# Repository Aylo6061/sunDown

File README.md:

# sunDown
Color temperature tunable lamp.

# Programming over USB
This program pulls the wifi credentials from a file stored in SPIFFS.  This file should be called "creds.txt" and needs to be added to /data.  The contents should be something like:

	{"ssid":"my_network_name", "pwd":"my_secret_password"}

This file is not included, for obvious reasons.  Once this file is in place, proceed to the next step.

Open sunDown.ino in the arduino IDE, and build/upload the code with ctrl+u or the upload button. Once this is done, use the [ESP32 sketch data upload](https://github.com/esp8266/arduino-esp8266fs-plugin) to upload the data folder.

This firmware uses [elegant ota](https://github.com/ayushsharma82/ElegantOTA). Refer to documentation there on running an OTA update.

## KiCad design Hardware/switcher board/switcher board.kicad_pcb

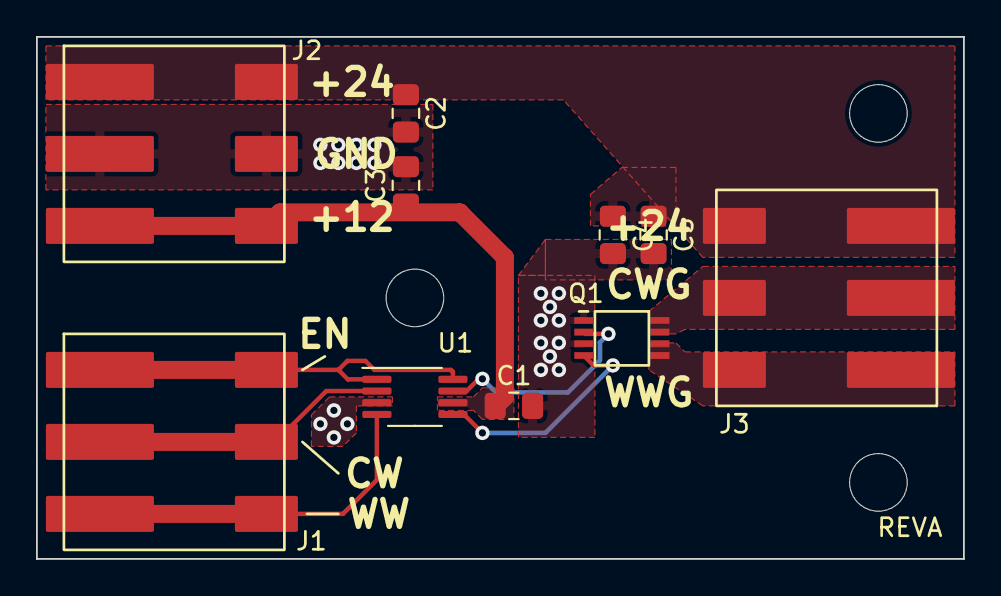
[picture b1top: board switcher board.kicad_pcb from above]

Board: 2 copper layers, 51.5 x 29.0 mm, 13 parts (0 on the bottom side), 10 nets.

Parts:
C1, C2, C3, C4, C5: C; C_0805_2012Metric_Pad1.18x1.45mm_HandSolder
H1, H2, H3: MountingHole; MountingHole_3.2mm_M3
J1, J2, J3: Screw_Terminal_01x03; 2060-453
Q1: IRF7503TRPBF; IR Micro8
U1: MCP14A0154-E/MS; MSOP-8_3x3mm_P0.65mm

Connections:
+12V: C1.1, C3.1, J1.3, U1.6 (Vdd)
+24V: C2.1, C4.1, C5.1, J1.1, J3.3
/CW: J2.2, U1.2 (IN_A)
/CW_Gnd: J3.2, Q1.7 (D2), Q1.8 (D2)
/EN: J2.1, U1.1 (EN_A), U1.8 (EN_B)
/WW: J2.3, U1.4 (IN_B)
/WW_Gnd: J3.1, Q1.5 (D2), Q1.6 (D2)
GND: C1.2, C2.2, C3.2, C4.2, C5.2, J1.2, Q1.1 (S2), Q1.3 (S2), U1.3 (GND)
unnamed: Q1.2 (G2), U1.7 (OUT_A)
unnamed: Q1.4 (G2), U1.5 (OUT_B)

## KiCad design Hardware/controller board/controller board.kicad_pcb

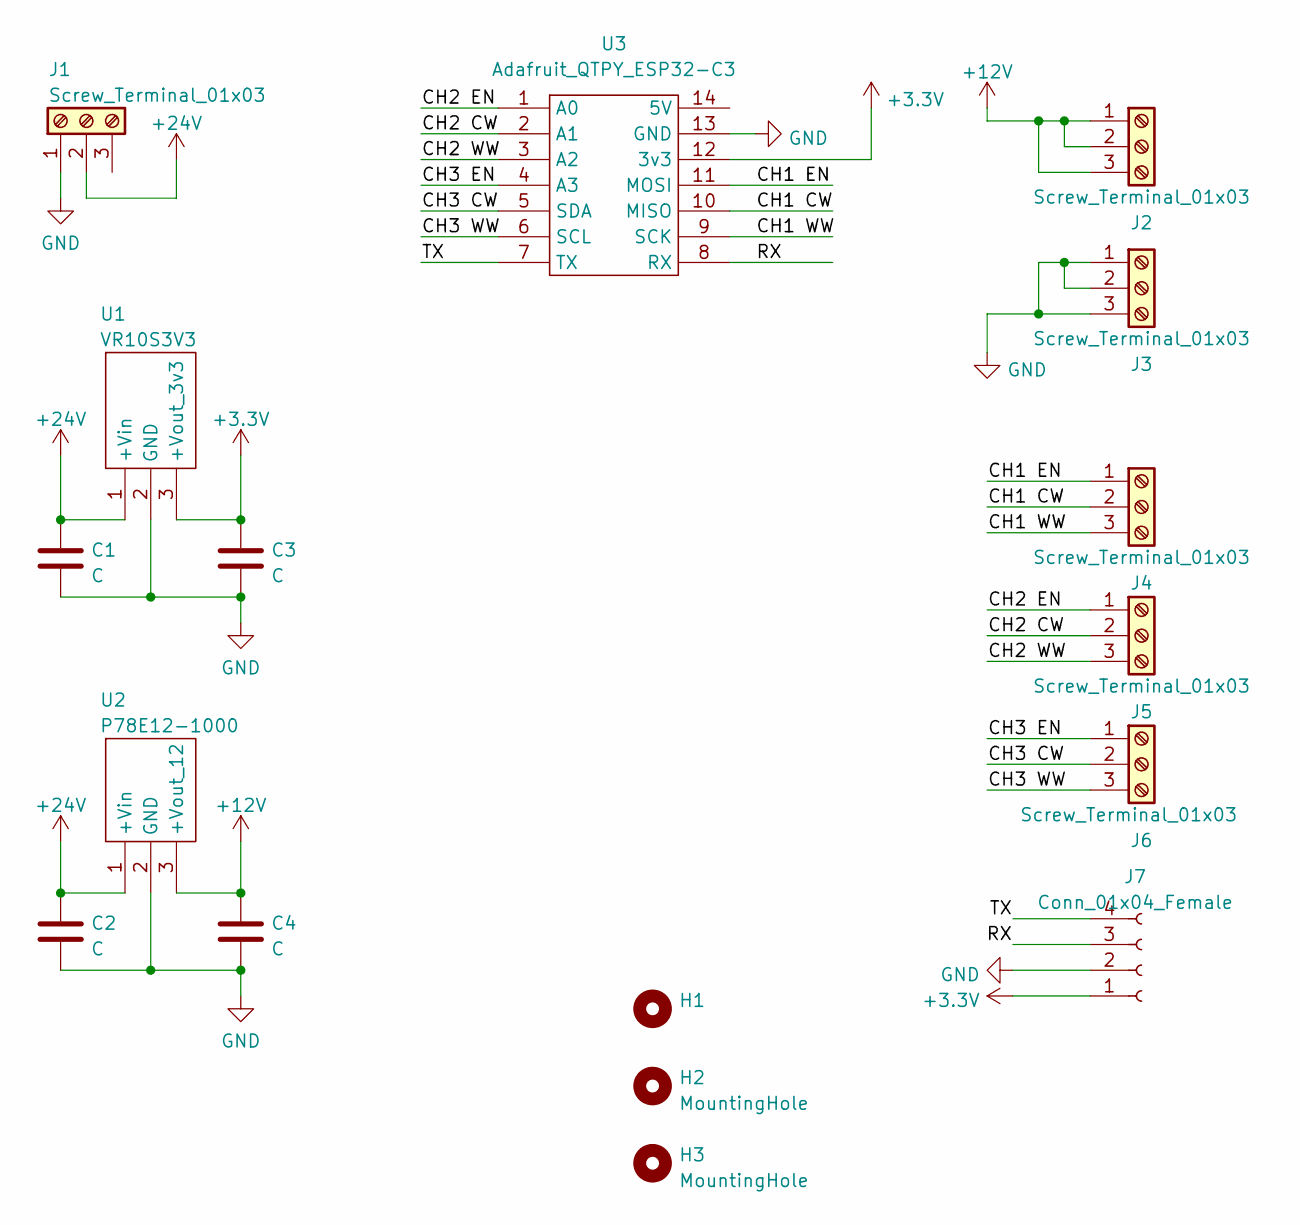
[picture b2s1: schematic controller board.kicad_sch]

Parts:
C1, C2, C3, C4: C; C_0805_2012Metric_Pad1.18x1.45mm_HandSolder
H1: (no value)
H2, H3: MountingHole
J1, J2, J3, J4, J5, J6: Screw_Terminal_01x03; 2060-453
J7: Conn_01x04_Female; PinHeader_1x04_P2.54mm_Vertical_SMD_Pin1Left
U1: VR10S3V3; 3pinDCDC
U2: P78E12-1000; 3pinDCDC
U3: Adafruit_QTPY_ESP32-C3; QTPY ESP32 C3_MSMD

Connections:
+3V3: C3.1, J7.1, U1.3 (+Vout_3v3), U3.12 (3v3)
+12V: C4.1, J2.1, J2.2, J2.3, U2.3 (+Vout_12)
+24V: C1.1, C2.1, J1.2, U1.1 (+Vin), U2.1 (+Vin)
/CH1 CW: J4.2, U3.10 (MISO)
/CH1 EN: J4.1, U3.11 (MOSI)
/CH1 WW: J4.3, U3.9 (SCK)
/CH2 CW: J5.2, U3.2 (A1)
/CH2 EN: J5.1, U3.1 (A0)
/CH2 WW: J5.3, U3.3 (A2)
/CH3 CW: J6.2, U3.5 (SDA)
/CH3 EN: J6.1, U3.4 (A3)
/CH3 WW: J6.3, U3.6 (SCL)
/RX: J7.3, U3.8 (RX)
/TX: J7.4, U3.7 (TX)
GND: C1.2, C2.2, C3.2, C4.2, J1.1, J3.1, J3.2, J3.3, J7.2, U1.2 (GND), U2.2 (GND), U3.13 (GND)

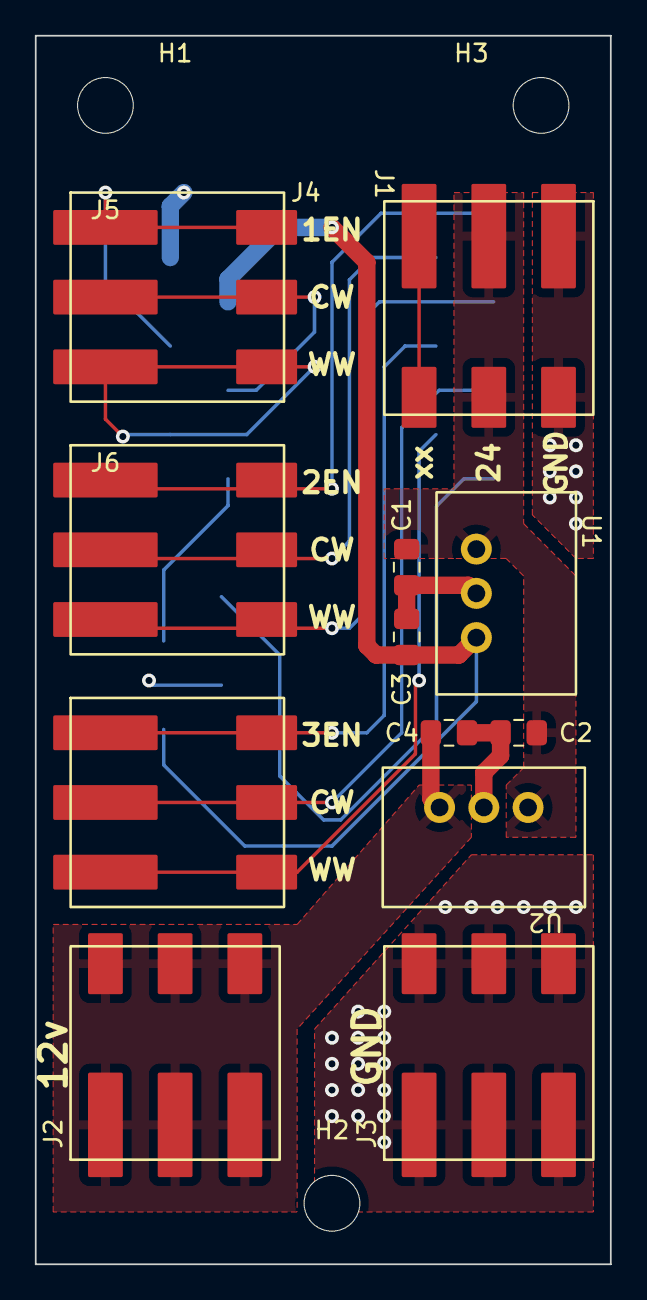
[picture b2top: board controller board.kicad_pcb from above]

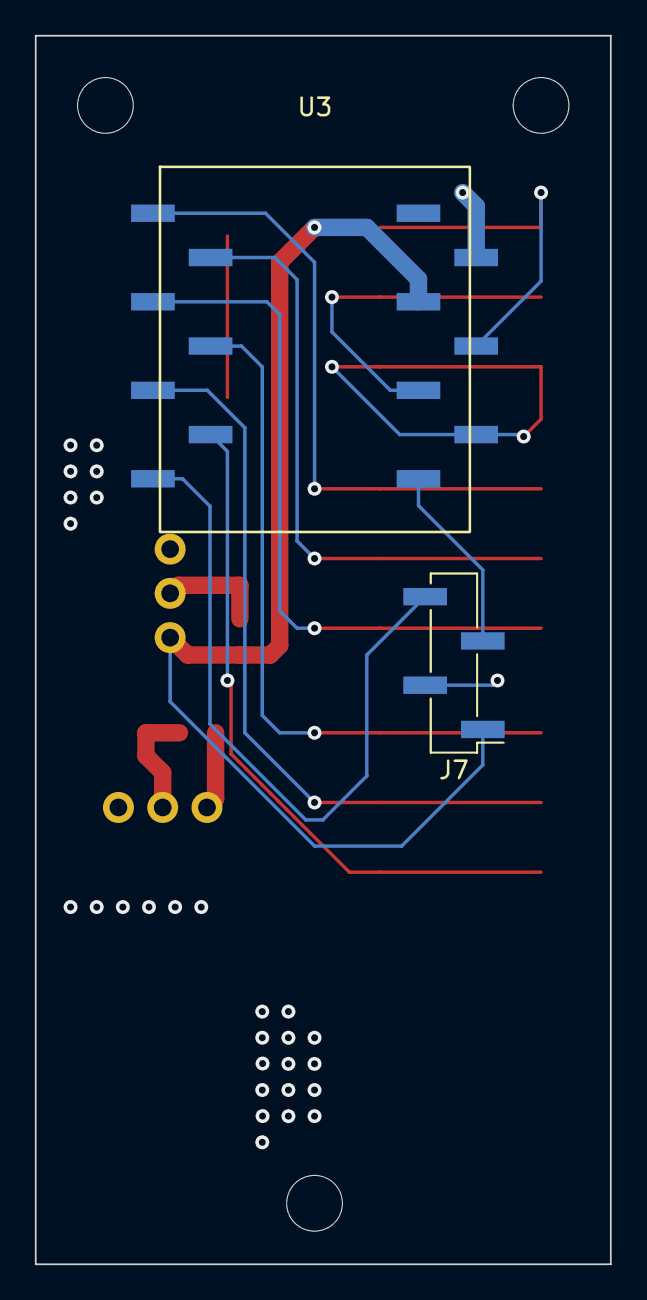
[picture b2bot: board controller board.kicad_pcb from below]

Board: 4 copper layers, 33.0 x 70.5 mm, 17 parts (2 on the bottom side), 15 nets.

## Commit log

2022-12-14 committing ignore and readme
2022-12-14 added firmware. not pretty but it works fine
2022-12-14 added hardware (PCB) files
2022-12-14 removed errant "u" in code.
2022-12-14 turn TX power all the way up
2022-12-21 fix reversed warm/cold slider in norm mode
2022-12-22 added state persistience + script to GET the state on page load
2023-10-21 get static ip. this is a little messy for obvious reasons, but it is nicer than having to get the ip over serial.
2023-10-21 changed ip to 10.0.0.55
2023-10-22 test version with sped up clock
2023-10-22 test stuff commented
